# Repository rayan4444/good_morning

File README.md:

# Curtain scheduler

Scheduled curtain control: opens and closes at specific times

# Mechanical
### Assets
* Fusion 360 link: https://a360.co/35GVD2y
* See release for STEP/STL files

### Improvements
* Add stiffness/ribs to reduce outer frame deflection
* smaller PCB mounting holes (changed diametr from 3mm to 2.7mm)
* larger chamfer to match curtain rail I have at home
* tighter tolerance on bearing holder
* choose a lighter/smaller motor bracket
* choos weaker/smaller mechanical end stops

# Electronics

### Description
Features:
* ESP32 WROOM32 module
* 1x button
* 1x programmable LED
* 1x VEML6030 ambient light sensor
* 1x CP2104 USB-UART bridge
* 1x DRV8825 stepper motor driver with controllable STEP, DIR, /SLEEP and /ENA

Power:
* 3S Lipo battery, charged externally - not by this board
* LDO for USB power during programming
* 12V-3.3V 1A switching regulator
* resistor divider to monitor battery voltage

>find out how long it lasts on 1 full charge

### Pinout
|Signal|Pin|Notes|
|:---:|:----:|:---:|
|Stepper_step|16||
|Stepper_direction|17||
|Stepper_enable|4|active low|
|Stepper_sleep|5|active low|
|Limit_switch_1|14|has external pullup (R23)|
|Limit_switch_2|12|no external pullup (R22), enable internal pullup|
|I2C_SCL|22||
|I2C_SDA|23||
|Ambient_light_sensor_int|21||
|LED|13||
|Button|15|enable internal pullup|
|Battery_voltage|I35, A1_7|ADC1 channel 7|

### Errata
* Remove R22: the external pullup messes with communication with flash when programming.
* Add 10k pull up resistor on the nENA line so that when the MCU is asleep the stepper is not enabled.

# Firmware

### Structure
* Wake up from sleep
* configure pins
* check battery level: if it is low blink the light and get stuck in this mode until the battery is recharged
* else, connect to wifi
* get time from NTP server
* check if it time to open/close the curtains
* open/close the curtains
* turn Wi-Fi OFF
* set wake up timer
* set wake up button
* go into deep sleep

> NOTE: this firmware version doesn't use the end stops to check the curtain status because the end stops I have are too strong and don't work. It will be updated once I find new end stops.

### Personal notes / improvements to do
* have a seperate RTC chip with less drift ?
* you can retain some simple things in RTC memory
```cpp
RTC_DATA_ATTR int bootCount = 0;
```
* change open/close times over wifi (from M5 stack core maybe?)
* "wireless wake up"?
* gather data from ambient light sensor over a week or so and see if there are any interesting patterns

### Reference links
* [deep sleep](https://lastminuteengineers.com/esp32-deep-sleep-wakeup-sources/)
* [NTP server](https://lastminuteengineers.com/esp32-ntp-server-date-time-tutorial/)
* [stepper driving with timers]()

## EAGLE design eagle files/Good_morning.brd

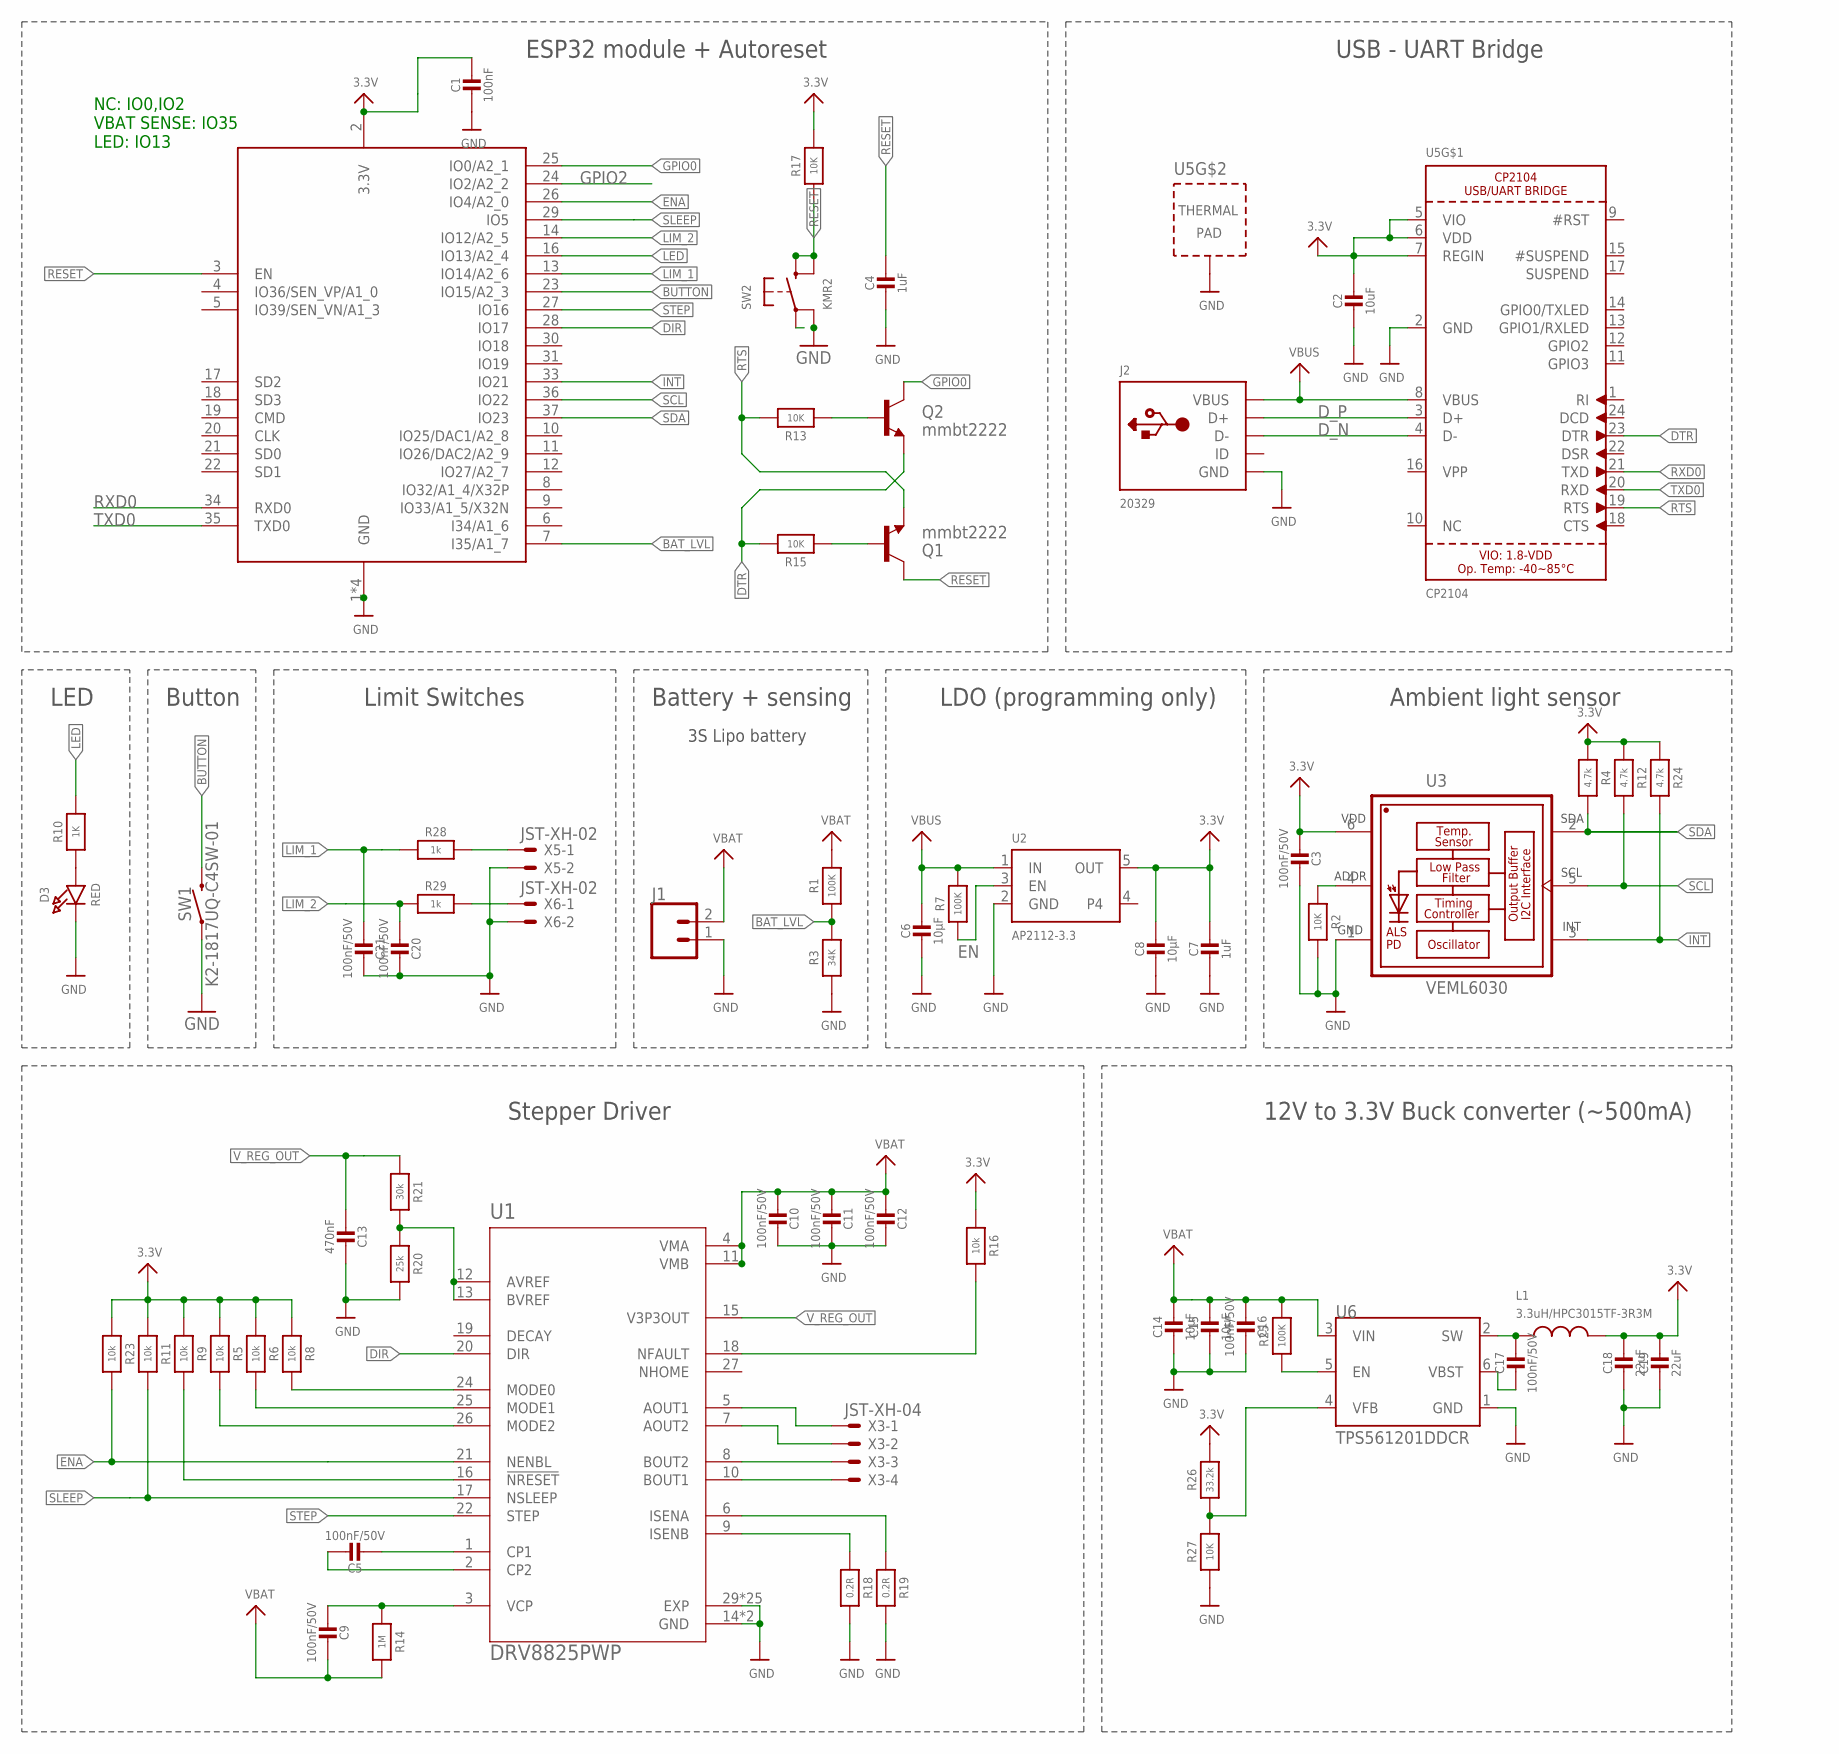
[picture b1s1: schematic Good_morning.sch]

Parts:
C1: 100nF; _0402
C2: 10uF; _0402
C3, C16, C17, C20, C21: 100nF/50V; _0402
C4, C7: 1uF; _0402
C5, C9, C10, C11, C12: 100nF/50V; _0805
C6, C8, C14, C15: 10µF; _0402
C13: 470nF; _0402
C18, C19: 22uF; _0402
D3: RED; CHIPLED_0805_NOOUTLINE
J1: CONN_023.5MM_LOCK; SCREWTERMINAL-3.5MM-2_LOCK
J2: 20329; 4UCONN_20329_V2
L1: 3.3uH/HPC3015TF-3R3M; WPN4020H100MT
Q1, Q2: mmbt2222; SOT23-3
R1, R7, R25: 100K; _0402
R2, R13, R15, R17, R27: 10K; _0402
R3: 34K; _0402
R4, R12, R24: 4.7k; _0402
R5, R6, R8, R9, R11, R16, R23: 10k; _0402
R10: 1K; _0402
R14: 1M; _0402
R18, R19: 0.2R; _1206
R20: 25k; _0402
R21: 30k; _0402
R26: 33.2k; _0402
R28, R29: 1k; _0402
SW1: K2-1817UQ-C4SW-01
SW2: KMR2; BTN_KMR2_4.6X2.8
U1: DRV8825PWP; SOP65P640X120-29N
U2: AP2112-3.3; SOT23-5
U3: VEML6030; VISHAY_VEML6030_2X2X0.87
U4: ESP32_WROOM32_SKINNY; WROOM32_SKINNY
U5: CP2104; QFN24_4MM_SMSC
U6: TPS561201DDCR; SOT95P280X110-6N
X3: JST-XH-04; JST-XH-04-PACKAGE-ROUND-PAD
X5, X6: JST-XH-02; JST-XH-02-PACKAGE-ROUND-PAD

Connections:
3.3V: C1.1, C2.1, C3.2, C7.1, C8.1, C18.1, C19.1, L1.2, R4.1, R5.1, R6.1, R8.1, R9.1, R11.1, R12.1, R16.1, R17.2, R23.1, R24.1, R26.1, U2.5 (OUT), U3.6 (VDD), U4.2 (3.3V), U5.5 (VIO), U5.6 (VDD), U5.7 (REGIN)
BAT_LVL: R1.1, R3.2, U4.7 (I35/A1_7)
BUTTON: SW1.P$2 (2), U4.23 (IO15/A2_3)
DIR: U1.20 (DIR), U4.28 (IO17)
DTR: Q2.2 (E), R15.2, U5.23 (DTR)
D_N: J2.D-, U5.4 (D-)
D_P: J2.D+, U5.3 (D+)
EN: R7.1, U2.3 (EN)
ENA: R23.2, U1.21 (NENBL), U4.26 (IO4/A2_0)
GND: C1.2, C2.2, C3.1, C4.2, C6.2, C7.2, C8.2, C10.1, C11.1, C12.1, C13.1, C14.2, C15.2, C16.1, C18.2, C19.2, C20.1, C21.1, D3.C, J1.1, J2.BASE@1 (GND), J2.BASE@2 (GND), J2.GND, J2.SPRT@1 (GND), J2.SPRT@2 (GND), J2.SPRT@3 (GND), J2.SPRT@4 (GND), R2.2, R3.1, R18.2, R19.2, R20.2, R27.1, SW1.P$1 (1), SW2.A' (P1), U1.14 (GND), U1.28 (GND), U1.29 (EXP), U1.P1 (EXP), U1.P2 (EXP), U1.P3 (EXP), U1.P4 (EXP), U1.P5 (EXP), U1.P6 (EXP), U1.P7 (EXP), U1.P8 (EXP), U1.P9 (EXP), U1.P10 (EXP), U1.P11 (EXP), U1.P12 (EXP), U1.P13 (EXP), U1.P14 (EXP), U1.P15 (EXP), U1.P16 (EXP), U1.P17 (EXP), U1.P18 (EXP), U1.P19 (EXP), U1.P20 (EXP), U1.P21 (EXP), U1.P22 (EXP), U1.P23 (EXP), U1.P24 (EXP), U2.2 (GND), U3.1 (GND), U4.1 (GND), U4.15 (GND), U4.38 (GND), U4.P$1 (GND), U5.2 (GND), U5.THERM (TP), U6.1 (GND), X5.2, X6.2
GPIO0: Q2.3 (C), U4.25 (IO0/A2_1)
GPIO2: U4.24 (IO2/A2_2)
INT: R24.2, U3.3 (INT), U4.33 (IO21)
LED: R10.1, U4.16 (IO13/A2_4)
LIM_1: C21.2, R28.1, U4.13 (IO14/A2_6)
LIM_2: C20.2, R29.1, U4.14 (IO12/A2_5)
unnamed: R2.1, U3.4 (ADDR)
unnamed: U1.8 (BOUT2), X3.3
unnamed: U1.10 (BOUT1), X3.4
unnamed: D3.A, R10.2
unnamed: R28.2, X5.1
unnamed: R25.1, U6.5 (EN)
unnamed: Q2.1 (B), R13.1
unnamed: R8.2, U1.24 (MODE0)
unnamed: R6.2, U1.25 (MODE1)
unnamed: R5.2, U1.26 (MODE2)
unnamed: Q1.1 (B), R15.1
unnamed: R9.2, U1.16 (!NRESET)
unnamed: C17.1, L1.1, U6.2 (SW)
unnamed: C5.2, U1.1 (CP1)
unnamed: C5.1, U1.2 (CP2)
unnamed: C9.2, R14.1, U1.3 (VCP)
unnamed: C17.2, U6.6 (VBST)
unnamed: R20.1, R21.2, U1.12 (AVREF), U1.13 (BVREF)
unnamed: R16.2, U1.18 (NFAULT)
unnamed: R29.2, X6.1
unnamed: U1.5 (AOUT1), X3.1
unnamed: U1.7 (AOUT2), X3.2
unnamed: R26.2, R27.2, U6.4 (VFB)
unnamed: R19.1, U1.6 (ISENA)
unnamed: R18.1, U1.9 (ISENB)
RESET: C4.1, Q1.3 (C), R17.1, SW2.B (S), SW2.B' (S1), U4.3 (EN)
RTS: Q1.2 (E), R13.2, U5.19 (RTS)
RXD0: U4.34 (RXD0), U5.21 (TXD)
SCL: R12.2, U3.5 (SCL), U4.36 (IO22)
SDA: R4.2, U3.2 (SDA), U4.37 (IO23)
SLEEP: R11.2, U1.17 (NSLEEP), U4.29 (IO5)
STEP: U1.22 (STEP), U4.27 (IO16)
TXD0: U4.35 (TXD0), U5.20 (RXD)
VBAT: C9.1, C10.2, C11.2, C12.2, C14.1, C15.1, C16.2, J1.2, R1.2, R14.2, R25.2, U1.4 (VMA), U1.11 (VMB), U6.3 (VIN)
VBUS: C6.1, J2.VBUS, R7.2, U2.1 (IN), U5.8 (VBUS)
V_REG_OUT: C13.2, R21.1, U1.15 (V3P3OUT)

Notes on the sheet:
NC: IO0,IO2 VBAT SENSE: IO35 LED: IO13
LDO (programming only)
Stepper Driver
LED
Button
ESP32 module + Autoreset
Battery + sensing
USB - UART Bridge
Limit Switches
3S Lipo battery
12V to 3.3V Buck converter (~500mA)
Ambient light sensor

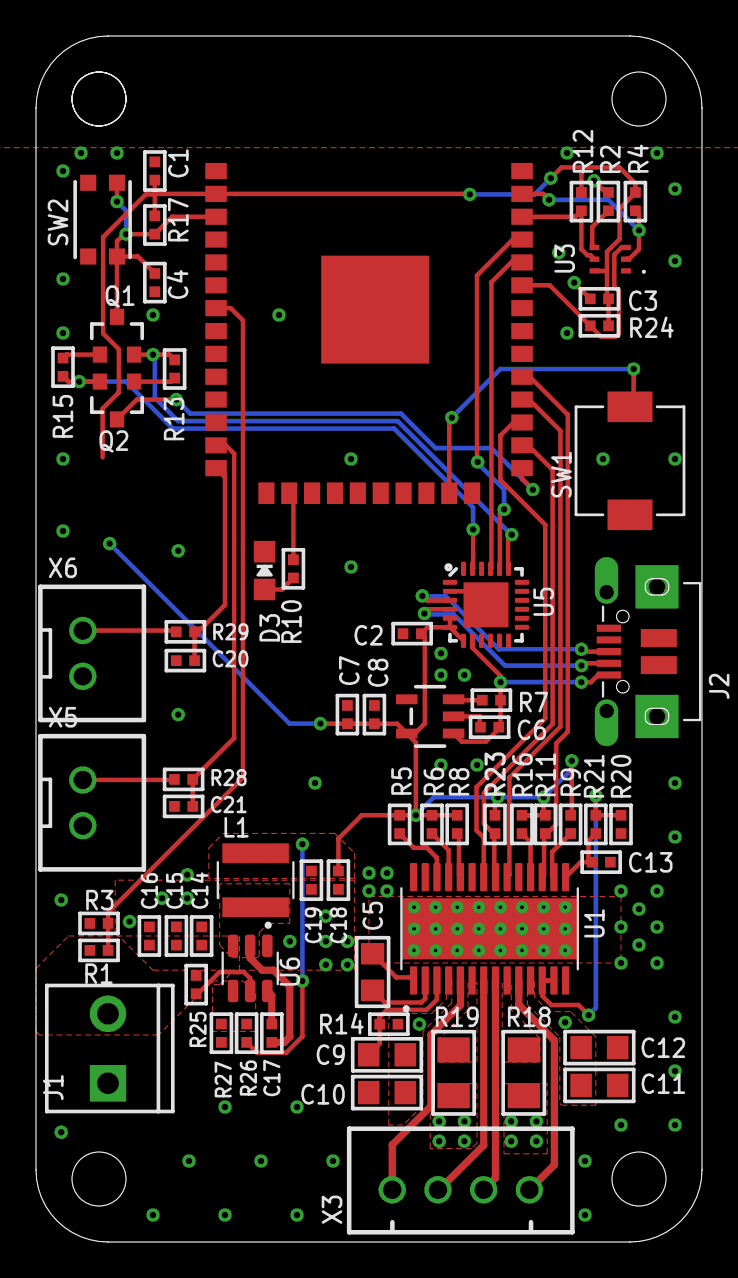
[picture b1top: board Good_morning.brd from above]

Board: 2 copper layers, 37.0 x 67.0 mm, 66 parts (0 on the bottom side), 51 nets.

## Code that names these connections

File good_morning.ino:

#include "Arduino.h"
#include <WiFi.h>

#define DEBUG

// time in between boot cycles
#define uS_TO_S_FACTOR 1000000 //Conversion factor for micro seconds to seconds
#define TIME_TO_SLEEP 30 //Time ESP32 will go to sleep (in seconds)

//math
const float pi = 3.14;

//pinout
#define led 13
#define step 16
#define dir 17
#define _ena 4
#define sleep 5
#define lim_1 14
#define lim_2 12
#define light_int 21
#define button 15 //also RTC_GPIO13
#define vbat 35

//flags
volatile bool button_pressed = 0;
volatile bool lim_1_reached = 0; //lim 1 reached means the curtain is fully open
volatile bool lim_2_reached = 0; //lim 2 reached means the curtain is fully closed
//WiFi credentials
const char* ssid = "XXX";
const char* password = "XXX";

//varialbles for time
const char* ntpServer = "pool.ntp.org";
const long gmtOffset_sec = 28800; //China is UTC+8 so offset: 8*3600 = 28800
const int daylightOffset_sec = 0; // China doesn't do Dailight saving so 0

//curtain open time
struct quand_t {
    int open_hour = 7;
    int open_min = 30;
    int open_late_hour = 10;
    int open_late_min = 30;
    int close_hour = 18;
    int close_min = 30;
} curtain;

//keeping the curtain status in memory during sleep
RTC_DATA_ATTR bool curtain_status = 0;

void setup()
{
    Serial.begin(115200);
    delay(1000);

    //print curtain status
    Serial.print("Curtain status: ");
    Serial.println(curtain_status);

    //check wake up reason
    print_wakeup_reason();

    //configure GPIO
    pinMode(led, OUTPUT);
    pinMode(step, OUTPUT);
    pinMode(dir, OUTPUT);
    pinMode(_ena, OUTPUT);
    pinMode(sleep, OUTPUT);
    pinMode(lim_1, INPUT);
    pinMode(lim_2, INPUT_PULLUP);
    pinMode(button, INPUT_PULLUP);
    pinMode(vbat, INPUT);

    //interrupts
    attachInterrupt(digitalPinToInterrupt(button), button_isr, FALLING);
    attachInterrupt(digitalPinToInterrupt(lim_1), lim_1_isr, FALLING);
    attachInterrupt(digitalPinToInterrupt(lim_2), lim_2_isr, FALLING);

    //setup stepper
    digitalWrite(_ena, HIGH);
    digitalWrite(sleep, HIGH);

    //if battery low, wake up every 5 seconds and blink the light but don't proceed
    if (vbat_low()){
        digitalWrite(led, HIGH);
        delay(1000);
        //Configure ESP wake up timer to 5s
        esp_sleep_enable_timer_wakeup(5 * uS_TO_S_FACTOR);
        //go back to sleep. the rest of the setup function will not run.
        esp_deep_sleep_start();
    }

    //connect to WiFi
    Serial.printf("Connecting to %s ", ssid);
    WiFi.begin(ssid, password);
    while (WiFi.status() != WL_CONNECTED) {
        Serial.print(".");
    }
    Serial.println(" CONNECTED");

    //init and get the time
    configTime(gmtOffset_sec, daylightOffset_sec, ntpServer);

    //handle the curtains
    curtaintime();

    //disconnect WiFi
    WiFi.disconnect(true);
    WiFi.mode(WIFI_OFF);

    //Configure ESP wake up timer to 5s
    esp_sleep_enable_timer_wakeup(TIME_TO_SLEEP * uS_TO_S_FACTOR);
    Serial.println("Setup ESP32 to sleep for every " + String(TIME_TO_SLEEP) + " Seconds");

    //Configure GPIO33 as ext0 wake up source for LOW logic level
    esp_sleep_enable_ext0_wakeup(GPIO_NUM_15, 0);

    //Go to sleep now
    esp_deep_sleep_start();
}

void loop()
{
}

void button_isr()
{
    // triggers when button is pressed
    button_pressed = 1;
    Serial.println("button pressed");
}

void lim_1_isr()
{
    //triggers when limit switch 1 is touched
    lim_1_reached = 1;
    Serial.println("limit swtch 1 pressed");
}

void lim_2_isr()
{
    //triggers when limit switch 2 is touched
    lim_2_reached = 1;
    Serial.println("limit swtch 2 pressed");
}

bool vbat_low()
{
    //true if the battery voltage is too low
    /* resistor divider 
    R1= 100k
    R2=34k
    (R2/(R1/R2))= 0.2537
    */

    int adc_raw = analogRead(vbat);
    float vref = 3.3;
    float voltage = vref * adc_raw;
    voltage = voltage / 4096.0;
    voltage = voltage / 0.237;

    // Serial.print("Battery voltage: ");
    // Serial.println(voltage);

    if (voltage < 9.0) {
        Serial.println("Battery low");
        return 1;
    } else {
        return 0;
    }
}

void curtaintime()
{
    struct tm timeinfo;
    if (!getLocalTime(&timeinfo)) {
        Serial.println("Failed to obtain time");
        return;
    }
    Serial.println(&timeinfo, "%A, %B %d %Y %H:%M:%S");
    int opening_hour, opening_min;
    // check opening time
    Serial.print("Day: ");
    Serial.println(timeinfo.tm_wday);
    if (timeinfo.tm_wday == 0) {
        opening_hour = curtain.open_late_hour;
        opening_min = curtain.open_late_min;
    } else {
        opening_hour = curtain.open_hour;
        opening_min = curtain.open_min;
    }
    //check if is time to open
    if (timeinfo.tm_hour == opening_hour) {
        //check minutes
        if (timeinfo.tm_min >= curtain.open_min) {
            
            if (!curtain_status){
            open_curtains();
            curtain_status=1;
            }else{
                Serial.println("curtain already open");
            }
        }
    }

    //check if it is time to close
    if (timeinfo.tm_hour == curtain.close_hour) {
        if (timeinfo.tm_min >= curtain.close_min) {
           if (curtain_status){
            close_curtains();
            curtain_status=0;           
           }
           else{
               Serial.println("curtain already closed");
           }
        }
    }
}


void open_curtains()
{
    Serial.println("curtains opening");
    move_stepper(-300); //move the stepper 20cm forward
}

void close_curtains()
{
    Serial.println("curtains closing");
    move_stepper(300); //move the stepper 20 cm back
}

void print_wakeup_reason()
{
    esp_sleep_wakeup_cause_t wakeup_reason;
    wakeup_reason = esp_sleep_get_wakeup_cause();
    switch (wakeup_reason) {
    case 1:
        Serial.println("Wakeup caused by external signal using RTC_IO");
        break;
    case 2:
        Serial.println("Wakeup caused by external signal using RTC_CNTL");
        break;
    case 3:
        Serial.println("Wakeup caused by timer");
        break;
    case 4:
        Serial.println("Wakeup caused by touchpad");
        break;
    case 5:
        Serial.println("Wakeup caused by ULP program");
        break;
    default:
        Serial.println("Wakeup was not caused by deep sleep");
        break;
    }
}

void move_stepper(int16_t distance) // distance in millimeters 
{
    // this will move the stepper in a direction for a set distance or until it hits an endstop

    // check direction
    if (distance < 0) {
        digitalWrite(dir, LOW);
        distance = -distance; // invert to keep positive math later
    } else {
        digitalWrite(dir, HIGH);
    }

    // enable stepper driver
    digitalWrite(_ena, LOW);
    digitalWrite(sleep, HIGH);

    // calculate step number
    //----------------------
    // 1 revolution = 360/1.8 = 200 steps
    // stepper driver is configured for 32 microsteps,1 revolution = 6400 microsteps.
    // diameter of timing belt gear: d = 25mm
    // 360 deg = 2*r*pi =>distance = d*pi*(deg/360) (mm)
    //distance = 25*pi*microsteps/6400
    // microsteps = distance *6400/(25*pi)
    uint32_t microsteps = (uint32_t)(6400 / (25 * pi));
    microsteps = distance * microsteps;

    for (int i = 0; i < microsteps; i++) {
        // check end stop flags
        if (lim_1_reached) {
            // disable the stepper
            digitalWrite(_ena, HIGH);
            digitalWrite(sleep, LOW);
            i = microsteps + 1; // exit the loop
            lim_1_reached=0;
            Serial.println("Stepper hit end stop");
        } else {
            // move by one microstep
            digitalWrite(step, HIGH);
            delayMicroseconds(50);
            digitalWrite(step, LOW);
            delayMicroseconds(50);
        }
    }
    Serial.println("Stepper done");
}

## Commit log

2020-01-10 Hardware files
2020-01-16 tested sleep, ntp, bat, interrupts
2020-01-25 updated readme, code to test
2020-01-25 fixes mentioned in readme errata
2020-01-26 working version (no end stops)

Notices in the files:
parts and their libraries:
microbuilder: This work is placed in the public domain, and may be freely used for commercial and non-commercial work with the following conditions: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
SparkFun-Connectors: Licensing: Creative Commons ShareAlike 4.0 International - https://creativecommons.org/licenses/by-sa/4.0
